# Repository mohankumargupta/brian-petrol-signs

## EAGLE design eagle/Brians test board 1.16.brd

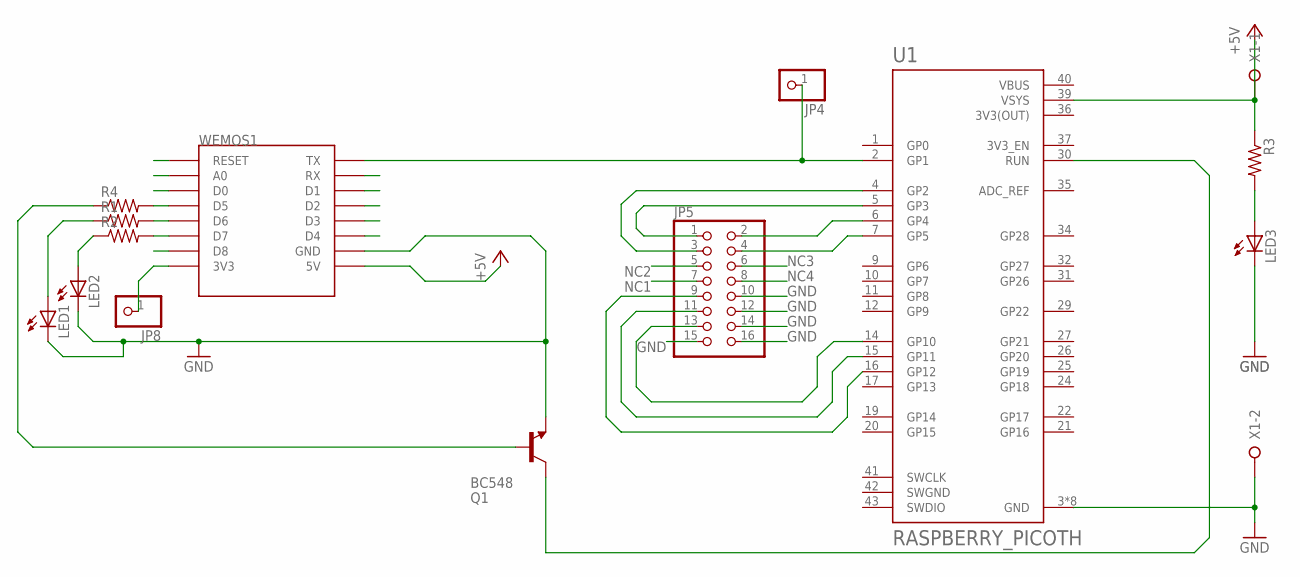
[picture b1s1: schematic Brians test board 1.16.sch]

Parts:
JP4, JP8: PINHD-1X1; 1X01
JP5: PINHD-2X8; 2X08
LED1, LED2, LED3: LED3MM
Q1: BC548; TO92-EBC
R1, R2, R4: R-US_0204/2V; 0204V
R3: R-US_0207/10; 0207/10
U1: RASPBERRY_PICOTH; PICO-PKG-TH
WEMOS1: WEMOS-D1-MINI
X1: W237-02P; W237-132

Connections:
3V3(OUT): U1.36 (3V3(OUT))
+5V: R3.1, U1.39 (VSYS), WEMOS1.5V, X1.1
A0: WEMOS1.A0
D0: WEMOS1.D0
D1: WEMOS1.D1
D2: WEMOS1.D2
D3: WEMOS1.D3
D4: WEMOS1.D4
D8: WEMOS1.D8
GND: JP5.10, JP5.12, JP5.14, JP5.15, JP5.16, LED1.K (C), LED2.K (C), LED3.K (C), Q1.E, U1.3 (GND), U1.8 (GND), U1.13 (GND), U1.18 (GND), U1.23 (GND), U1.28 (GND), U1.33 (GND), U1.38 (GND), WEMOS1.GND, X1.2
unnamed: JP5.1, U1.5 (GP3)
unnamed: JP8.1, WEMOS1.3V3
unnamed: Q1.C, U1.30 (RUN)
unnamed: JP4.1, U1.2 (GP1), WEMOS1.TX
unnamed: JP5.3, U1.4 (GP2)
unnamed: R2.2, WEMOS1.D7
unnamed: JP5.13, U1.14 (GP10)
unnamed: JP5.11, U1.15 (GP11)
unnamed: JP5.9, U1.16 (GP12)
unnamed: JP5.2, U1.6 (GP4)
unnamed: JP5.4, U1.7 (GP5)
unnamed: R1.2, WEMOS1.D6
unnamed: LED2.A, R2.1
unnamed: LED1.A, R1.1
unnamed: LED3.A, R3.2
unnamed: R4.2, WEMOS1.D5
unnamed: Q1.B, R4.1
NC1: JP5.7
NC2: JP5.5
NC3: JP5.6
NC4: JP5.8
RST: WEMOS1.RESET
RX: WEMOS1.RX
SWGND: U1.42 (SWGND)
VBUS: U1.40 (VBUS)

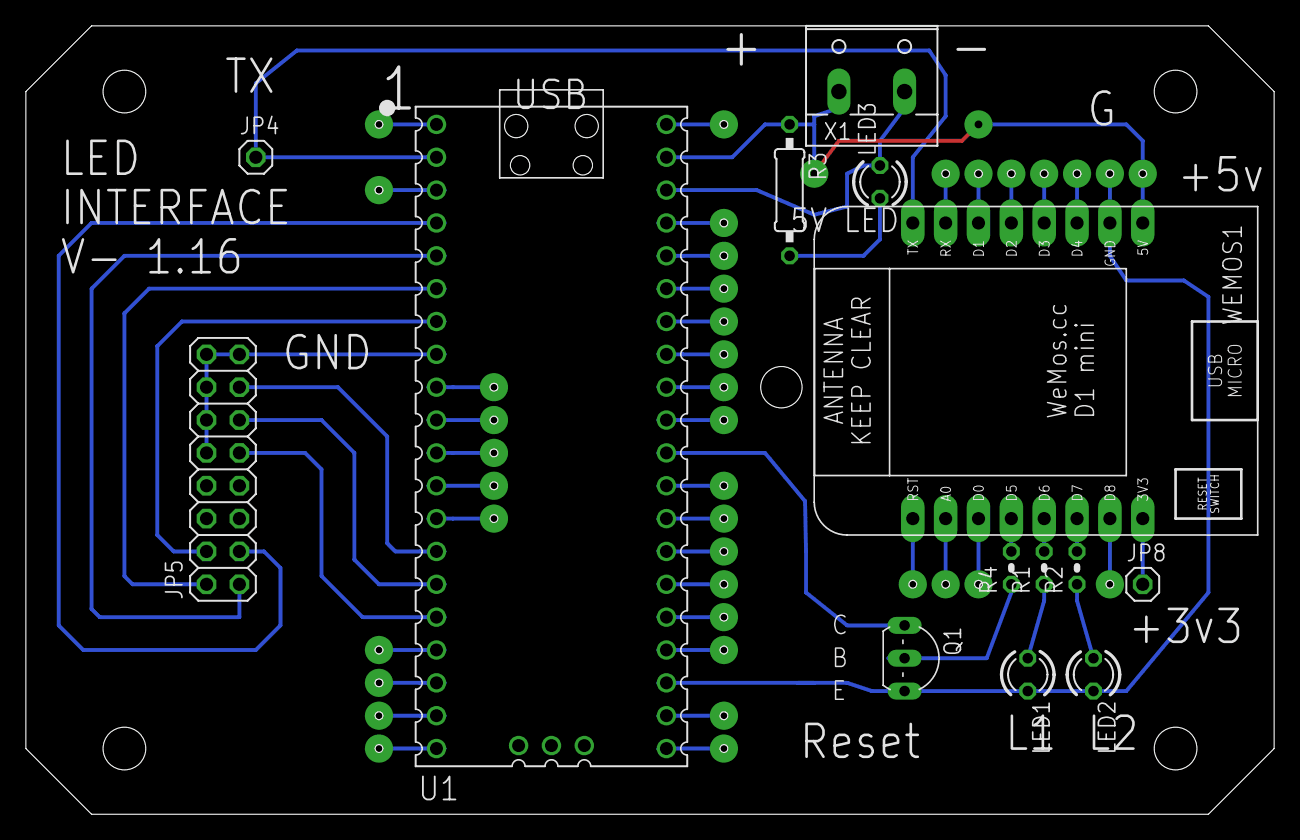
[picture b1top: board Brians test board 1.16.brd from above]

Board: 2 copper layers, 96.5 x 61.0 mm, 14 parts (0 on the bottom side), 19 nets.
